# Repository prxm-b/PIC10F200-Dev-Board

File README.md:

# PIC10F200-Dev-Board

Dev board for Pic 10F200IOT
- Features acces to all the MCU pins (the whole 6 !)
- USB-C for power input (no power delivery available :P )

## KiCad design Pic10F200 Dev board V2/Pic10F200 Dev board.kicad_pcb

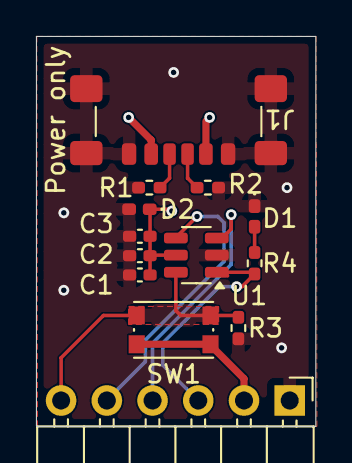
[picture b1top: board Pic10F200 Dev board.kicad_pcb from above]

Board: 4 copper layers, 15.5 x 21.7 mm, 13 parts (0 on the bottom side), 9 nets.

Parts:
C1: 10u; C_0402_1005Metric_Pad0.74x0.62mm_HandSolder
C2: 1u; C_0402_1005Metric_Pad0.74x0.62mm_HandSolder
C3: 100n; C_0402_1005Metric_Pad0.74x0.62mm_HandSolder
D1: LED; LED_0402_1005Metric_Pad0.77x0.64mm_HandSolder
D2: PTVS5V0Z1USK; D_0402_1005Metric_Pad0.77x0.64mm_HandSolder
J1: USB_C_Receptacle_PowerOnly_6P; USB_C_Receptacle_GCT_USB4135-GF-A_6P_TopMnt_Horizontal
J2: Conn_01x06_Pin; PinHeader_1x06_P2.54mm_Horizontal
R1, R2: 5.1k; R_0402_1005Metric_Pad0.72x0.64mm_HandSolder
R3: 100k; R_0402_1005Metric_Pad0.72x0.64mm_HandSolder
R4: 2.1k; R_0402_1005Metric_Pad0.72x0.64mm_HandSolder
SW1: SW_Push; SW_Push_1P1T_NO_CK_KMR2
U1: PIC10F200-IOT; SOT-23-6

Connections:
+5V: C1.1, C2.1, C3.1, D2.1 (K), J1.A9 (VBUS), J1.B9 (VBUS), J2.2, SW1.1, U1.5 (VDD)
/GP0: J2.3, R4.1, U1.1 (GP0)
/GP1: J2.4, U1.3 (GP1)
/GP2: J2.5, U1.4 (GP2)
/GP3: J2.6, R3.2, SW1.2, U1.6 (GP3)
GND: C1.2, C2.2, C3.2, D1.1 (K), D2.2 (A), J1.A12 (GND), J1.B12 (GND), J1.S1 (SHIELD), J2.1, R1.1, R2.1, R3.1, U1.2 (VSS)
unnamed: D1.2 (A), R4.2
unnamed: J1.A5 (CC1), R2.2
unnamed: J1.B5 (CC2), R1.2

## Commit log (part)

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2026-04-29 Initial Commit, Added Kicad PCB Project and MPLABX Project
2026-04-29 Update README.md
    Add description in Readme.md
2026-04-29 Cleaned Schematic and PCB layout
2026-04-30 Added different vibe coded examples as a demo for the dev board
2026-06-02 Added Schematic of PCB in PDF
